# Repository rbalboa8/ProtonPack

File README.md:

[![Contributors][contributors-shield]][contributors-url]
[![Forks][forks-shield]][forks-url]
[![Stargazers][stars-shield]][stars-url]
[![Issues][issues-shield]][issues-url]
[![MIT License][license-shield]][license-url]
[![Twitter][Twitter-shield]][Twitter-url]

<!-- PROJECT LOGO -->
<br />
<p align="center">

  <h3 align="center">GhostKitty Proton Pack</h3>

  <p align="center">
  This is my contribution to the GB community. This project adds a bit more movie / game accuracy but also a little fun :)

<!-- TABLE OF CONTENTS -->
## Table of Contents

* [About the Project](#about-the-project)
  * [Built With](#Build-Requirements)
* [Getting Started](#getting-started)
  * [Prerequisites](#prerequisites)
  * [Wand Configuration](#wand-configuration)  
* [License](#license)
* [Contact](#contact)
* [Acknowledgements](#acknowledgements)

<!-- ABOUT THE PROJECT -->
## About The Project

<div align="center">
  YouTube Video<br />

Original Prototype <br />
</p>

Afterlife Cyclotron 40 segment LED ring<br />
</p>
</div>

I want this to be a source for anyone to use to create their own proton pack kits for as cheap as possible and still include all the features for a rumble motor, 2 firing mechanisms, all functioning LEDs in the wand, pack themes, full 28 segment bar graph, and an output for a vent kit.

**Current Themes for the pack:**
*  Movie
*  Stasis / Afterlife
*  Slime
*  Meson
*  Christmas!
*  *Future* Halloween

### Getting Started

### Build Requirements:

*  1 - Arduino Nano (Amazon)  
*  1 - DFPlayer Mini (Be aware that some of the knock offs do not perform correctly, reference to the busy pin may not work) (Digikey Only)
*  1 - Any amplifing circuit (Currently testing an Adafruit Stereo 20W Class D Audio Amplifier - MAX9744)  (Amazon, Digikey)
*  1 - LED Matrix Driver - HT16K33 Breakout (for the bar graph) (Amazon, Digikey)
*  1 - 28 segment bargraph (barmeter.com, ebay is your best option)
*  1 - Pack of neopixels or equivalent WS2812B ( Vent and wand LEDs) (Amazon)
*  1 - LED strip (Powercell)  (Amazon)
*  1 - Adafruit Jewel - Wand Tip (WAs looking at the Pixie but there is a concern of its overhead requirements when working with normal WS2812B's, and they can not be chained together with WS2812B's) (Amazon, Digikey)
*  1 - 40 Segment LED ring or LED strip (WS2812B's) - Afterlife Cyclotron LED
*  Pack of 24 awg stranded cable (Amazon) - To keep things clean you might want to look at ribbon cables or multi conductor cables.
*  For circuit noise filtering, I would add a 1000uF electrolytic capacitors closes to the neopixels, and a 470 Ohm resistor before the first led of the strip (This is recommended by Adafruit as well). I would recommend one 1000uF capacitor for the wand to filter out noise from both the bargraph and the neopixels. (See Diagram)
*  If you are printing the PCB you will need a RJ45 Connector, 2.54mm JST Connectors, 2.54mm Dupont Connectors, 1 MP1584EN Buck Converter, 7805 Voltage regulator, 2 1k Ohm resistors, and some 0.1 uF and 0.33 uF ceramic capacitors. Additionally for the wand, 1000uF capacitor, a 1N4001 diode and a transistor.

### Prerequisites

You are going to need to install the following libraries:

**For the Audio DFPlayer Player:**
*  SoftwareSerial.h
*  DFPlayerMini_Fast.h

**For the WS2812B / NeoPixel LEDs**
*  Adafruit_NeoPixel.h

**Custom Libraries for the Powercell / Cyclotron / Bargraph Animiations**
*  GBLEDPatternsJewel.h
*  BGSequence.h

**Sound Files for the DFPlayer or Alternative Player**

<a href="https://mega.nz/file/R5sWzCha#zm4DIskyvmF08JNp8MnOAEqCDmNe2MSCN6wtFMExKlU">Here are some sound files I found online or mixed myself</a>

### Wand Configuration

<!-- CONTRIBUTING -->
## Contributing

Contributions are what make the open source community such an amazing place to be learn, inspire, and create. Any contributions you make are **greatly appreciated**.

1. Fork the Project
2. Create your Feature Branch (`git checkout -b feature/AmazingFeature`)
3. Commit your Changes (`git commit -m 'Add some AmazingFeature'`)
4. Push to the Branch (`git push origin feature/AmazingFeature`)
5. Open a Pull Request

<!-- LICENSE -->
## License

Distributed under the MIT License. See `LICENSE` for more information.

<!-- CONTACT -->
## Contact

Mike Simone - [@mikesimone3](https://twitter.com/mikesimone3)

Project Link: [https://github.com/MikeS11/ProtonPack](https://github.com/MikeS11/ProtonPack)

<!-- ACKNOWLEDGEMENTS -->
## Acknowledgements

*  Eric Banker for the for the wonder work completed on his Arduino project. (a couple of his functions are referenced in this project)
* 
* 

<!-- MARKDOWN LINKS & IMAGES -->
<!-- https://www.markdownguide.org/basic-syntax/#reference-style-links -->
[contributors-shield]: https://img.shields.io/github/contributors/MikeS11/ProtonPack.svg?style=flat-square
[contributors-url]: https://github.com/MikeS11/ProtonPack/graphs/contributors
[forks-shield]: https://img.shields.io/github/forks/MikeS11/ProtonPack.svg?style=flat-square
[forks-url]: https://github.com/MikeS11/ProtonPack/network/members
[stars-shield]: https://img.shields.io/github/stars/MikeS11/ProtonPack.svg?style=flat-square
[stars-url]: https://github.com/MikeS11/ProtonPack/stargazers
[issues-shield]: https://img.shields.io/github/issues/MikeS11/ProtonPack.svg?style=flat-square
[issues-url]: https://github.com/MikeS11/ProtonPack/issues
[license-shield]: https://img.shields.io/github/license/MikeS11/ProtonPack.svg?style=flat-square
[license-url]: https://github.com/MikeS11/ProtonPack/blob/master/LICENSE.txt
[twitter-shield]: https://img.shields.io/badge/-Twitter-black.svg?style=flat-square&logo=Twitter&colorB=555
[twitter-url]: https://Twitter.com/mikesimone3
[product-screenshot]: Media/Images/README_Images/screenshot.png

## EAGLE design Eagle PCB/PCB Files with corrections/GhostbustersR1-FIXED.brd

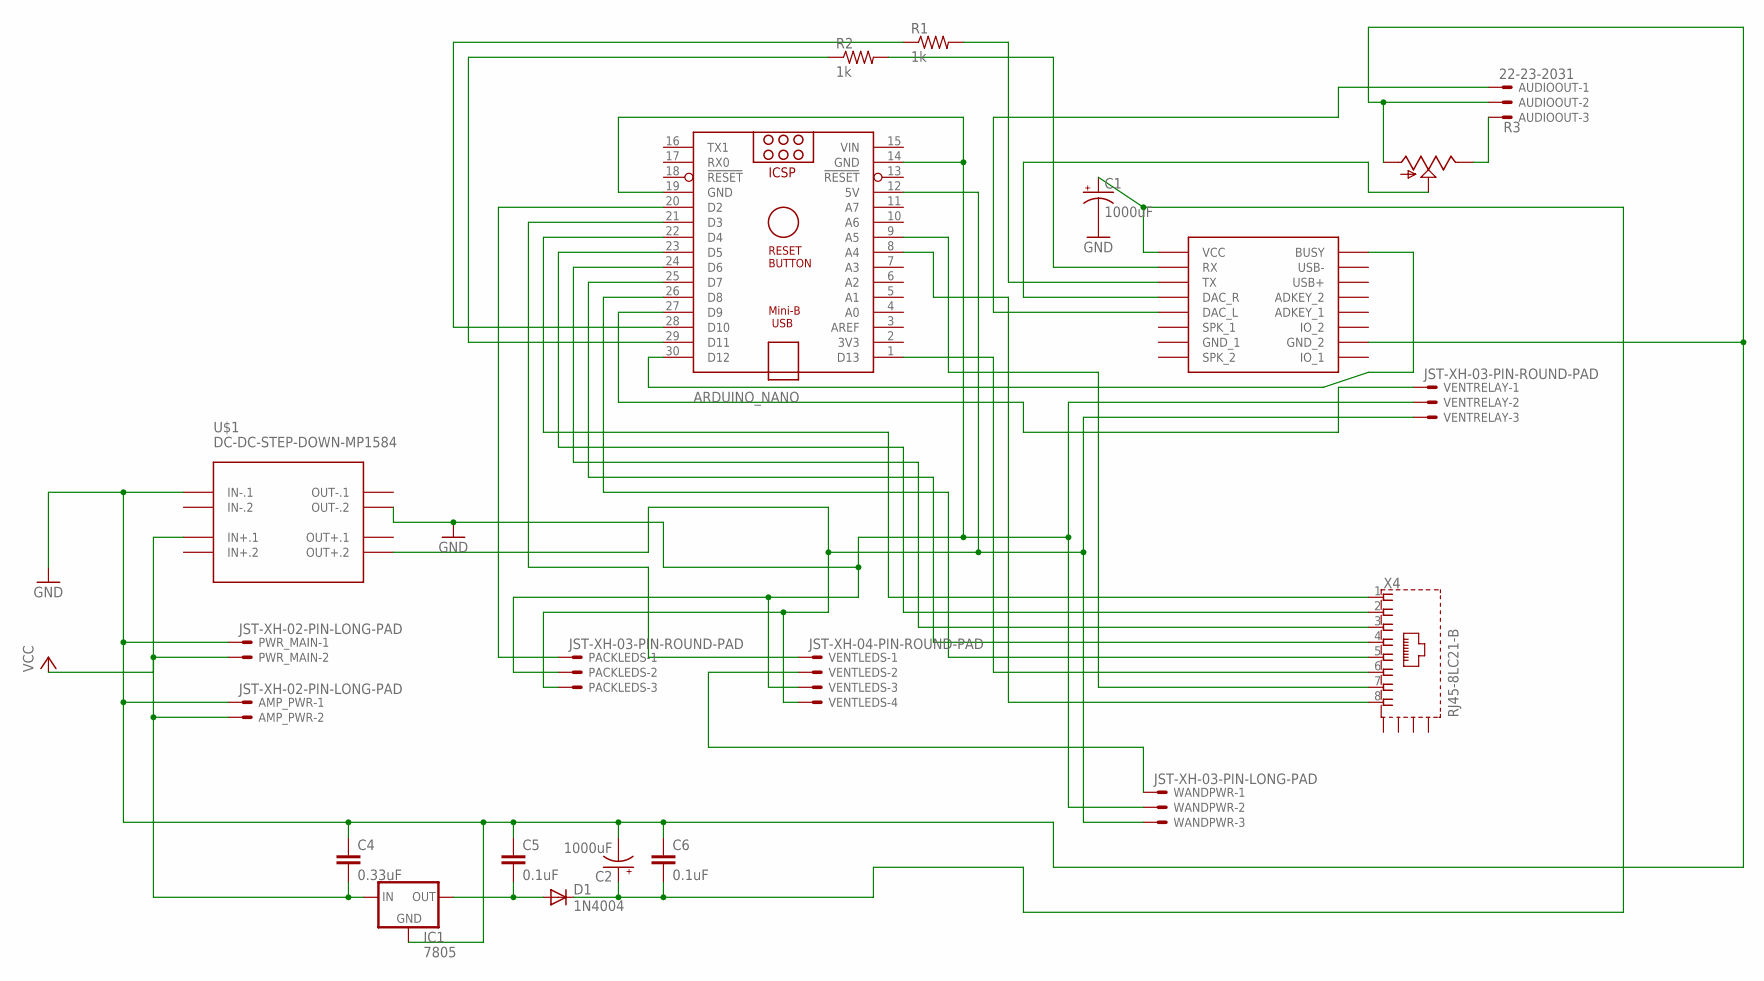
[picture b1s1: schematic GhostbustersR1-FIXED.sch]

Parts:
AMP_PWR: JST-XH-02-PIN-LONG-PAD; JST-XH-02-PACKAGE-LONG-PAD
ARDUINO_NANO: ARDUINO_NANO
AUDIOOUT: 22-23-2031
C1, C2: 1000uF; E3,5-8
C4: 0.33uF; C2.5-4
C5, C6: 0.1uF; C2.5-4
D1: 1N4004; DO41-10
DFPLAYER: DFPLAYER
IC1: 7805; 78MXXS
PACKLEDS: JST-XH-03-PIN-ROUND-PAD; JST-XH-03-PACKAGE-ROUND-PAD
PWR_MAIN: JST-XH-02-PIN-LONG-PAD; JST-XH-02-PACKAGE-LONG-PAD
R1, R2: 1k; 0207/12
R3: TRIM_US-B64Y; B64Y
U$1: DC-DC-STEP-DOWN-MP1584
VENTLEDS: JST-XH-04-PIN-ROUND-PAD; JST-XH-04-PACKAGE-ROUND-PAD
VENTRELAY: JST-XH-03-PIN-ROUND-PAD; JST-XH-03-PACKAGE-ROUND-PAD
WANDPWR: JST-XH-03-PIN-LONG-PAD; JST-XH-03-PACKAGE-LONG-PAD
X4: RJ45-8LC21-B; RJ45-SHIELD1

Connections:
GND: AMP_PWR.1, ARDUINO_NANO.14 (GND), ARDUINO_NANO.19 (GND), AUDIOOUT.2, C1.-, C2.-, C4.1, C5.1, C6.1, DFPLAYER.GND_2, IC1.GND, PACKLEDS.2, PWR_MAIN.1, R3.A, U$1.IN-.1, U$1.OUT-.2, VENTLEDS.3, VENTRELAY.2, WANDPWR.2
unnamed: ARDUINO_NANO.12 (5V), PACKLEDS.3, U$1.OUT+.2, VENTLEDS.4, VENTRELAY.3, WANDPWR.3
unnamed: ARDUINO_NANO.25 (D7), X4.4
unnamed: AUDIOOUT.3, R3.E
unnamed: ARDUINO_NANO.29 (D11), R2.1
unnamed: ARDUINO_NANO.28 (D10), R1.1
unnamed: ARDUINO_NANO.20 (D2), PACKLEDS.1
unnamed: ARDUINO_NANO.21 (D3), VENTLEDS.1
unnamed: VENTLEDS.2, WANDPWR.1
unnamed: ARDUINO_NANO.22 (D4), X4.1
unnamed: ARDUINO_NANO.23 (D5), X4.2
unnamed: ARDUINO_NANO.24 (D6), X4.3
unnamed: ARDUINO_NANO.26 (D8), X4.5
unnamed: ARDUINO_NANO.1 (D13), X4.6
unnamed: ARDUINO_NANO.30 (D12), DFPLAYER.BUSY
unnamed: DFPLAYER.DAC_R, R3.S
unnamed: AUDIOOUT.1, DFPLAYER.DAC_L
unnamed: ARDUINO_NANO.27 (D9), VENTRELAY.1
unnamed: ARDUINO_NANO.8 (A4), X4.8
unnamed: ARDUINO_NANO.9 (A5), X4.7
unnamed: DFPLAYER.TX, R1.2
unnamed: DFPLAYER.RX, R2.2
unnamed: C5.2, D1.A, IC1.OUT
unnamed: C1.+, C2.+, C6.2, D1.C, DFPLAYER.VCC
VCC: AMP_PWR.2, C4.2, IC1.IN, PWR_MAIN.2, U$1.IN+.1
VIN: ARDUINO_NANO.15 (VIN)

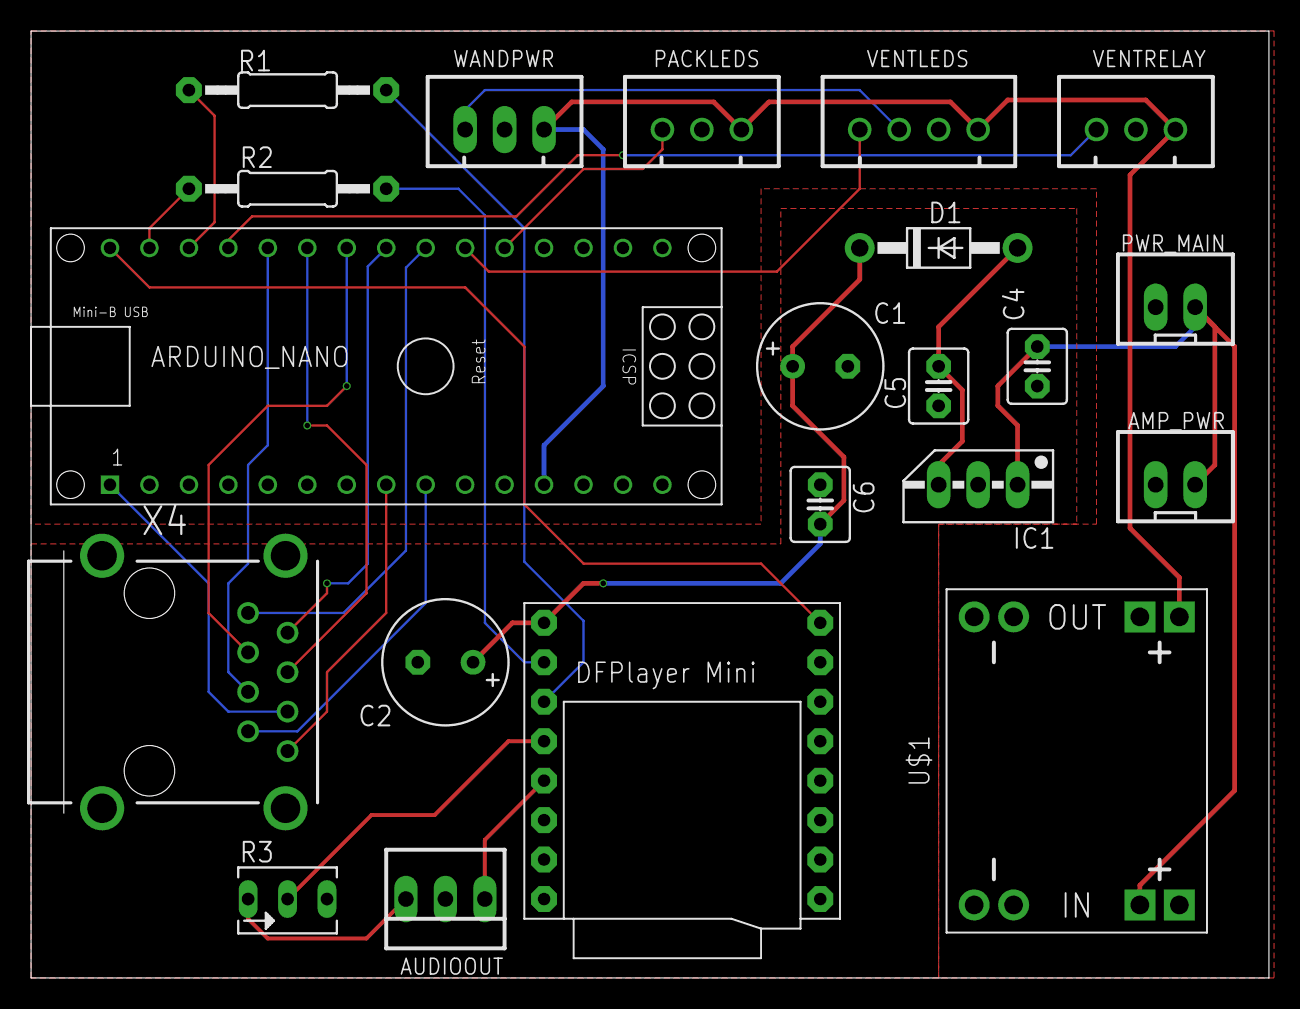
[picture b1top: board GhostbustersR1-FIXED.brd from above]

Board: 2 copper layers, 79.7 x 60.9 mm, 21 parts (0 on the bottom side), 25 nets.

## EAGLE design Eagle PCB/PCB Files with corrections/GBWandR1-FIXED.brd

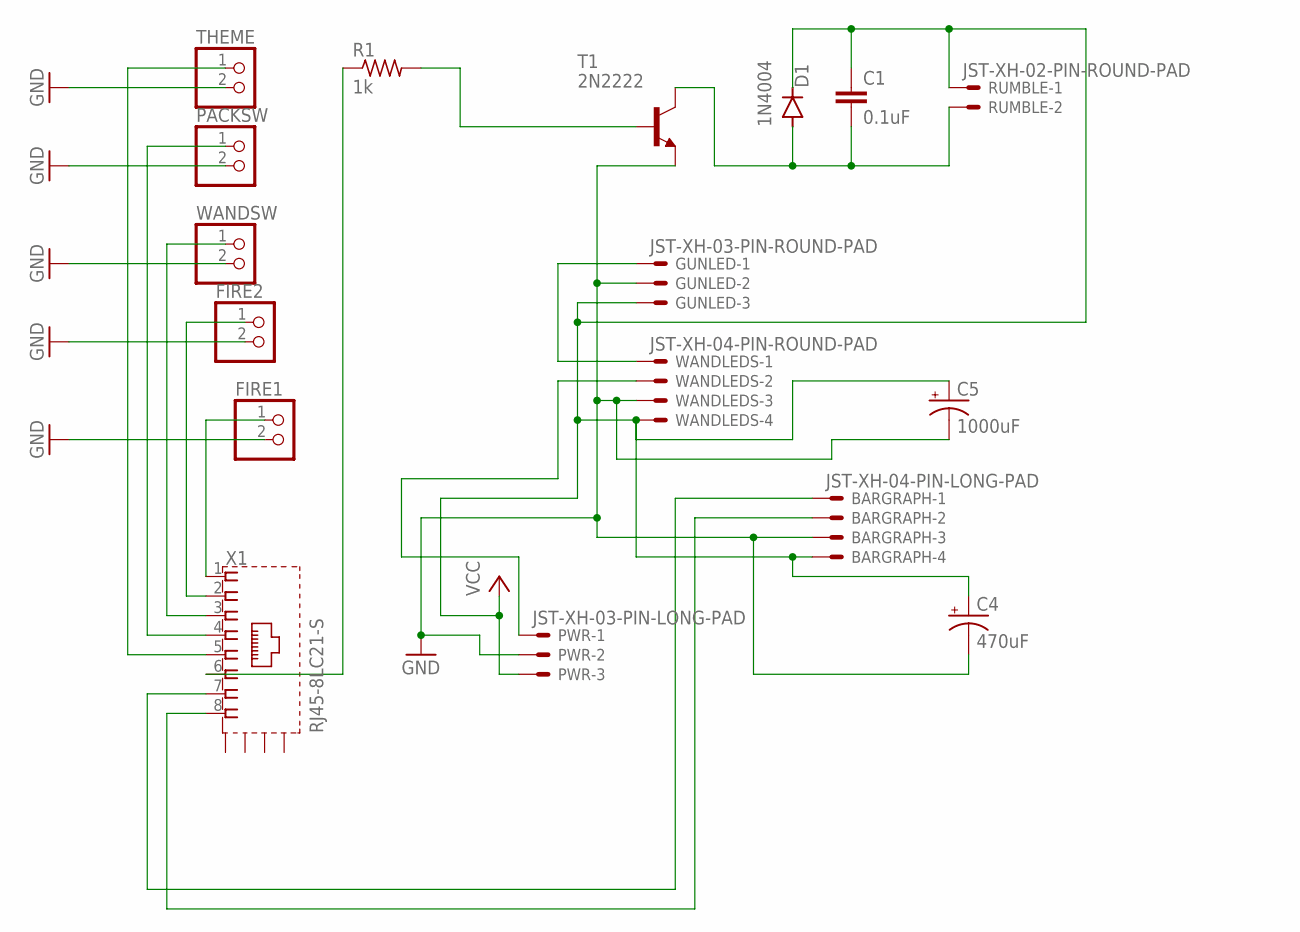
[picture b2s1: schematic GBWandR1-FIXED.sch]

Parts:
BARGRAPH: JST-XH-04-PIN-LONG-PAD; JST-XH-04-PACKAGE-LONG-PAD
C1: 0.1uF; C050-024X044
C4: 470uF; E3,5-8
C5: 1000uF; E3,5-8
D1: 1N4004; DO41-10
FIRE1, FIRE2: PINHD-1X2; 1X02
GUNLED: JST-XH-03-PIN-ROUND-PAD; JST-XH-03-PACKAGE-ROUND-PAD
PACKSW: PINHD-1X2; 1X02
PWR: JST-XH-03-PIN-LONG-PAD; JST-XH-03-PACKAGE-LONG-PAD
R1: 1k; 0207/9
RUMBLE: JST-XH-02-PIN-ROUND-PAD; JST-XH-02-PACKAGE-ROUND-PAD
T1: 2N2222; TO92-EBC-OVAL
THEME: PINHD-1X2; 1X02
WANDLEDS: JST-XH-04-PIN-ROUND-PAD; JST-XH-04-PACKAGE-ROUND-PAD
WANDSW: PINHD-1X2; 1X02
X1: RJ45-8LC21-S; RJ45-SHIELD1

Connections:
GND: BARGRAPH.3, C4.-, C5.-, FIRE1.2, FIRE2.2, GUNLED.2, PACKSW.2, PWR.2, T1.E, THEME.2, WANDLEDS.3, WANDSW.2
unnamed: PWR.1, WANDLEDS.2
unnamed: FIRE1.1, X1.1
unnamed: FIRE2.1, X1.2
unnamed: WANDSW.1, X1.3
unnamed: PACKSW.1, X1.4
unnamed: THEME.1, X1.5
unnamed: GUNLED.1, WANDLEDS.1
unnamed: R1.1, X1.6
unnamed: R1.2, T1.B
unnamed: BARGRAPH.2, X1.8
unnamed: BARGRAPH.1, X1.7
unnamed: C1.2, D1.A, RUMBLE.2, T1.C
VCC: BARGRAPH.4, C1.1, C4.+, C5.+, D1.C, GUNLED.3, PWR.3, RUMBLE.1, WANDLEDS.4

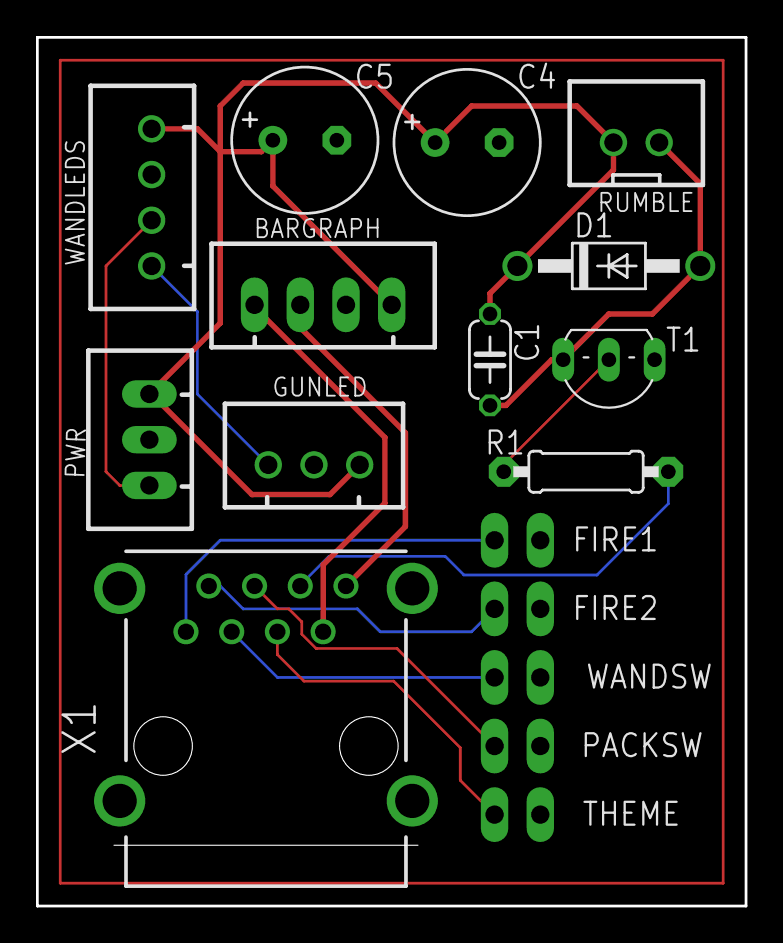
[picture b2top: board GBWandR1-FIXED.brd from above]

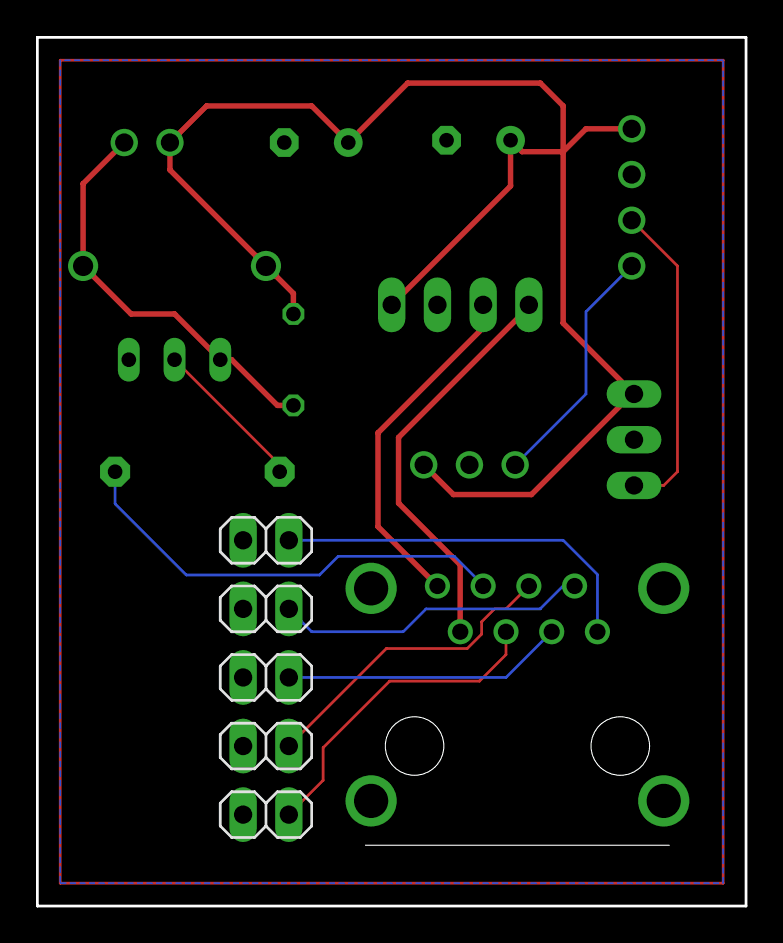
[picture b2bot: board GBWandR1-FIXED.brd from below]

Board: 2 copper layers, 39.4 x 48.3 mm, 17 parts (5 on the bottom side), 14 nets.

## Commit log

2022-07-06 moved original files for archiving
2022-07-06 add .gitignore
2022-07-06 remove DS_Store file
2022-07-06 Images of eagle of reported issues and images of the areas of the board to fix
2022-07-06 Additional PCB to make wiring the Bargraph to the HT16K33 driver board easier and compact
2022-07-06 Original schematic and board files you can edit using the Easy EDA application
2022-07-06 Gerber files ready to submit if you are using JLCPCB as your board provider. These have been tested as working.
2022-07-06 Schematic and Board files for Eagle with my changes
2022-07-06 Proton Pack PCB Schematic file for the Eagle application
2022-07-06 Proton Pack PCB board file for the Eagle application
2022-07-06 Proton Pack Wand PCB board file for the Eagle application
2022-07-06 Proton Pack Wand PCB schematic file for the Eagle application
2022-07-06 Clear image of the original wiring of the main board. It shows the routing og the top layer, in RED, and the bottom layer, in BLUE. There are lines that cross at the input of the R1/R2 resistors, the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
2022-07-06 Clearer image showing the changes made to the original PCB line routing on the main board of the Proton Pack. This can be used to compare with the originals routing and for checking before ordering. 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
2022-07-06 Clearer image showing the changes made to the original PCB line routing on the Wand board of the Proton Pack. This can be used to compare with the originals routing and for checking before ordering. 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
2022-07-06 An all layer image showing full Wand board of the Proton Pack including the routing changes that I have made to the original design
2022-07-06 An all layer image showing full Main board of the Proton Pack including the routing changes that I have made to the original design
2022-07-06 The Wand PCB board Gerber files ready to upload if you are using JLCPCB as your board provider. WARNING use at your own risk. these files are Untested so please use the original eagle files to check 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
2022-07-06 The Main Proton Pack PCB board Gerber files ready to upload if you are using JLCPCB as your board provider. WARNING use at your own risk. these files are Untested so please use the original eagle fil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
2022-07-06 Issues reported by Eagle for the Main proton pack PCB
2022-07-06 Issues reported by Eagle for the Wand PCB
2022-07-06 changed 'PowerCellLEDs' value to address issue when using 2x8Bit LED boards for the powercell. after the start up sequence the top LED would stay lit if using a value less than 16 LEDs in the main co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
2022-07-06 changed 'NeoPixelLEDCount1' to use 15 Bits as the PowerCell number
2022-07-06 Original line changed as relay started on untill wand start up switch was toggled
2022-07-06 sound effect files for the DFPlayer Mini sourced from the MikeS11 Github
2022-07-07 gitignore updated
2022-07-07 sounds removal
2022-07-07 re-upload sounds
2022-07-07 readme file
2022-07-07 Error report images update
2022-07-07 updated gitignore
2022-07-07 STL rumble motor bracket to attach to the wand wall
2022-07-07 Updated Wand Rumble Motor Mount STL
2022-07-07 Booster Tube Lid Mod to secure with magnets
2022-07-07 Bracket to guide the cables and Smoke tubes on the motherboard
2022-07-07 Bracket to mount the Cyclotron Lights to the motherboard rather than inside the shell
2022-07-07 Jig to aid drilling the holes on the L-Bracket to mount the shell to the motherboard
2022-07-07 N-Filter Vent smoke kit motherboard mount and Booster tube refill carridge for the Kanger T3S
2022-07-07 Power Cell Motherboard mounting bracket
2022-07-07 Bracket to mount the MikeS11 main PCB and TPA3116D2 amplifier to the motherboard
2022-07-07 Mod of the inner barrel of the Wand pop mechanism to allow installation of 3bit pcb in a 28mmOD/24.8mmID Aluminium tube
2022-07-07 Bracket to mount the MikeS11 Wand PCB inside the Wand
2022-07-08 Brackets to allow easy installation/removal and cable management of 1bit led PCBs in to the wand
2022-07-08 Updated BRD files
2022-07-08 The Wand Gerber files ready to upload if you are using JLCPCB as your board provider. WARNING use at your own risk. These files are untested so please use the Eagle files to check for issues that may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
2022-07-08 The Main Proton Pack PCB board Gerber files ready to upload if you are using JLCPCB as your board provider. WARNING use at your own risk. these files are Untested so please use the eagle files to che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
2022-07-08 Examples of the PCB boards look and function
2022-07-08 moved original PCB images
2022-07-08 Images added of the installed electronics of the N-Filter smoke kit with printed parts
2022-07-08 Images of the completed PCBs with soldered parts in place
2022-07-08 Original PCB Layout Images moved
2022-07-08 Images of the traces to cut, marked in black and the placement of wires to replace traces. NOTE: Those cut lines near the white line of the Nano outline must be made carefully in those exact points. 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
2022-07-10 move image
2022-07-10 In progress parts used list
2022-12-04 remove jlcpcb json file
2022-12-04 remove old file
2022-12-04 spacing change
2022-12-04 commented code added for bargraphs that use a common cathode. Edoardo Tavilla, ref Facebook group Arduino for Ghostbusters Props
2022-12-04 Original bargraph+driver PCB design. Compatible with the original code
2022-12-04 Compatible with the original code. Silkscreen updated to identify as common Anode bargraph compatible pcb.
2022-12-04 Comommon Cathode bargraph compatible PCB. Code changes required. See supplied images for details.
2022-12-04 Code changes instructions
2022-12-04 BGSequence.h changes.
2022-12-04 Unit example
2022-12-04 EasyEDA Design files
2022-12-20 error correction to bargraph code
2022-12-21 file removal
2022-12-21 Corrections to the Common Anode/Cathode Labels
2022-12-21 Preprepared Gerber files compatible with JLCPCB for the ALTERNATIVE barmeter. Code changes required
2022-12-21 files removed
2022-12-21 Preprepared Gerber files compatible with JLCPCB for the ORIGINAL CODE COMPATIBLE barmeter.
2022-12-21 PCB traces image
2022-12-21 Original code changes post/instructions from the Facebook group
2022-12-21 Project files for editing
2022-12-21 Images of Top and Bottom Traces
2022-12-21 Example image of purchased original code compatible barmeter
2022-12-21 Schematics image
2022-12-30 Written Guide to setting up the Arduino IDE software and how to upload the project code to your Arduino
2022-12-30 2nd draft edits
2023-01-11 wiring diagram
2023-01-11 Updates to Code installation guide
2023-01-11 document updates
2023-01-11 Wiring diagram updates
2023-01-11 guide updates
2023-01-23 organising
2023-01-23 New in-shell mounting stls
2023-01-23 New in-shell electronicas mounting 3D printed mounting brackets
2023-01-23 file caretaking
2023-01-23 Cyclotron stls and STEP files
2023-01-24 Version updates
2023-02-02 Version one of the rail mounting system fixed inside the crank generator
2023-02-02 Version two of the rail mounting system fixed inside the crank generator
2023-08-08 Wiring diagram correction, bargraph Clock/Data lines
2023-11-28 Made comments clearer
2023-11-28 File names updated
2023-11-28 Files deleted
2023-11-28 Made it clearer which bargrapg goes with which PCB. Files relabelled due to miss identified components.
2024-07-25 Bargraph Library change - stops bargrph flash when power is plugged in
2024-07-31 README.md removal
2024-07-31 Clean slate for repo reorganization
2024-07-31 gitignore update
2024-07-31 Mikes README added back with images
2024-07-31 Original code added back but organised and changelog.md file added
2024-07-31 Media directory added. Original audio files added back.
2024-07-31 Bargraph PCB files added back and organised
2024-07-31 README.md for the Bargraph PCB Updated.
2024-07-31 gitignore updated to ignore *.pages files
2024-07-31 Mikes11 original breadboard circuit diagram of the proton pack wiring.
2024-07-31 Added - R.Carruthers Arduino Code Installation Guide
2024-07-31 Moved the README_Images directory
2024-09-12 Add files via upload
    Guide for beginners, how to get the project PCBs manufactured.
2025-07-12 Original Project Files Backup
2025-07-12 Arduino projects reorganised and updates to Bargraph+HT16K33 libraries
2025-07-12 config.h files updated so both options are commented by default
2026-01-06 Adding Bin directory
2026-01-06 Bargraph library re-upload
2026-01-06 Deleted directory
2026-01-06 Bin file

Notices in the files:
parts and their libraries:
diy-modules: Released under the Creative Commons Attribution 4.0 International License: http://creativecommons.org/licenses/by/4.0
